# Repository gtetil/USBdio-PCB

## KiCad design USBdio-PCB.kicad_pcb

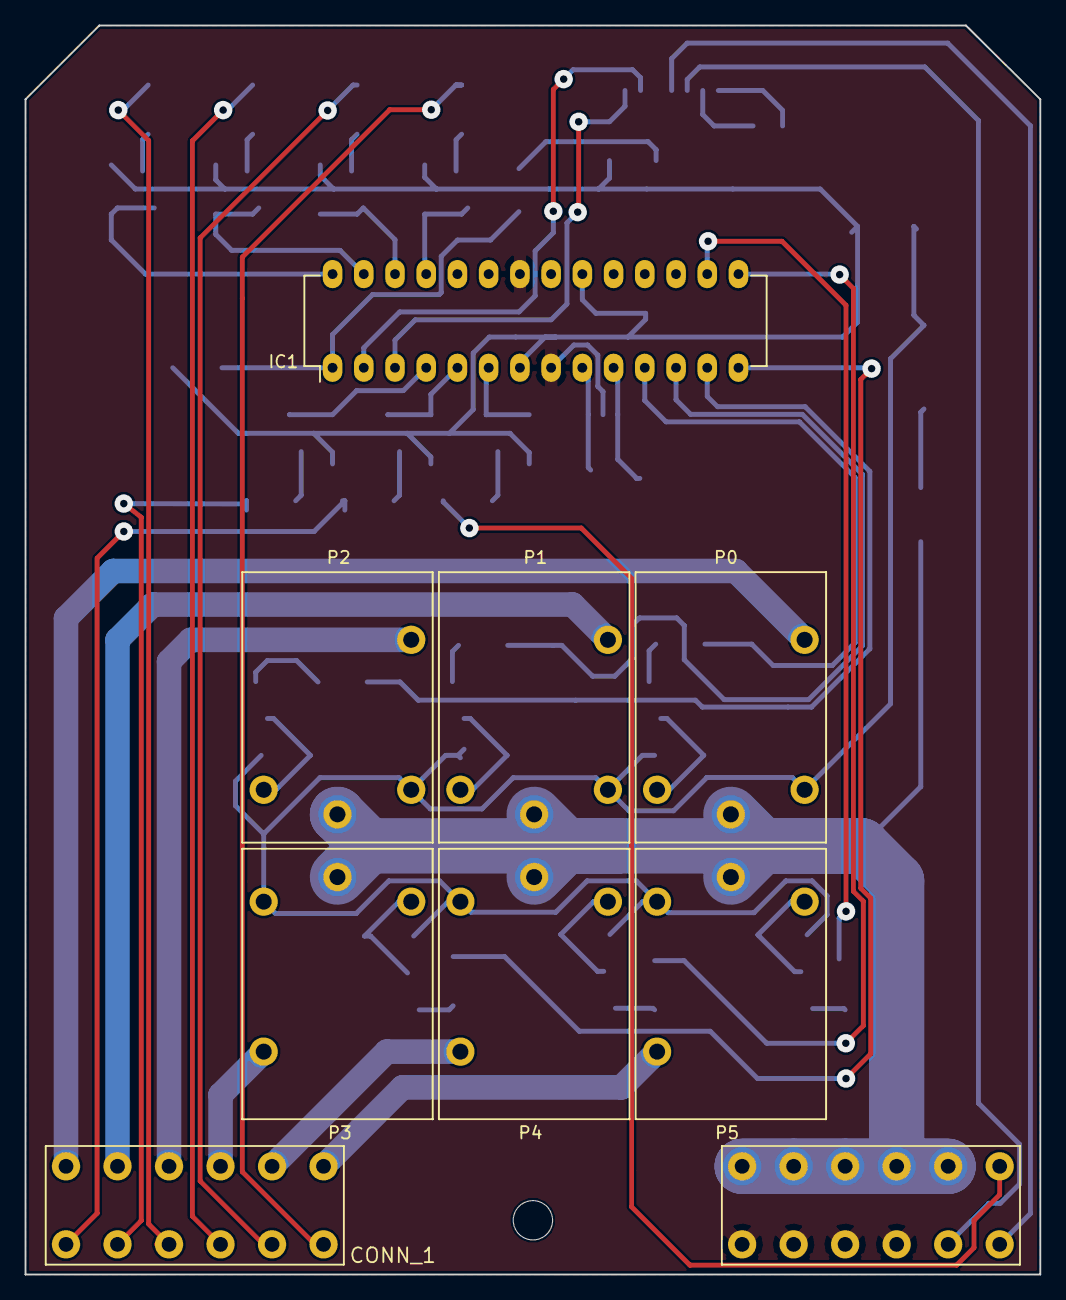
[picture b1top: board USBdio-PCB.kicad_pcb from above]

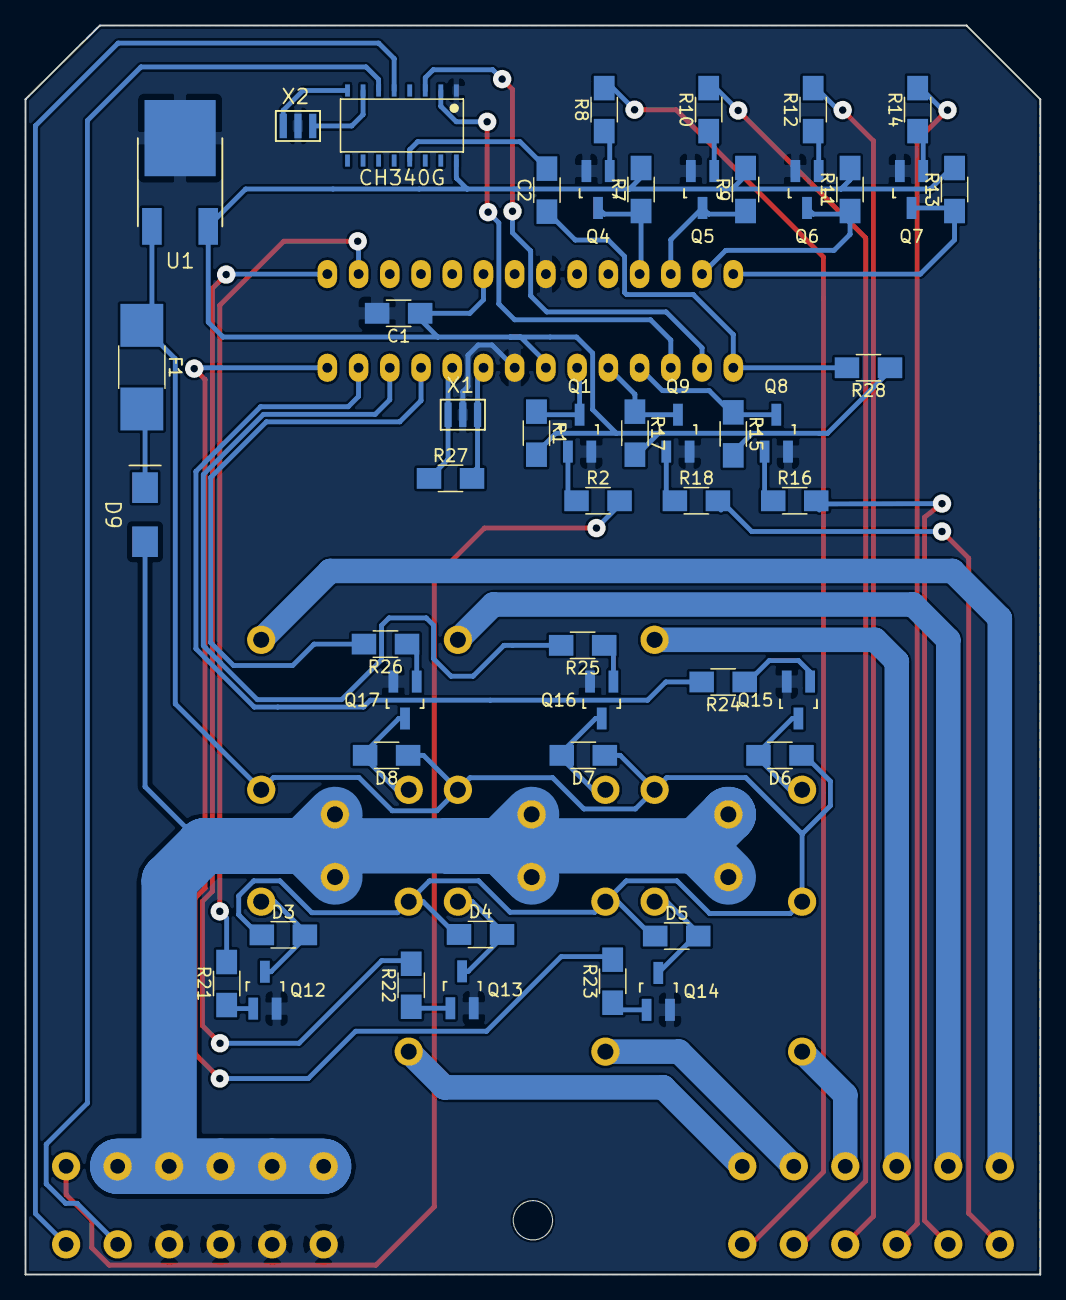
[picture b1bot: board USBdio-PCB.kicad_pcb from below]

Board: 2 copper layers, 82.5 x 101.6 mm, 57 parts (49 on the bottom side), 60 nets.

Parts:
C1, C2: 0.1uF; R_1206_HandSoldering_(narrow)
CONN_1: DEUTSCH_CONN_(DTM13-12PA-12PB-R008)
D3, D4, D5, D6, D7, D8: D; R_1206_HandSoldering_(narrow)
D9: D_Schottky; SCHOTTKY_(PMEG3030EP,115)
F1: Polyfuse; R_1812_HandSoldering
IC1: ATMEGA328-P; DIP-28_W7.62mm_LongPads
IC2: CH340G
P0, P1, P2, P3, P4, P5: RELAY_(JSM1A-12V-4)
Q1, Q4, Q5, Q6, Q7, Q8, Q9: Q_NPN_BEC; SOT-23_Handsoldering
Q12, Q13, Q14, Q15, Q16, Q17: Q_NPN; SOT-23_Handsoldering
R1, R2, R7, R8, R9, R10, R11, R12, R13, R14, R15, R16, R17, R18, R28: 10k; R_1206_HandSoldering_(narrow)
R21, R22, R23, R24, R25, R26: 680; R_1206_HandSoldering_(narrow)
R27: 1M; R_1206_HandSoldering_(narrow)
U1: NCV7805BDTRKG; REGULATOR_(NCV7805BDTRKG)
X1, X2: Crystal_GND2; RESONATOR_(CSTCE16M0V53C-R0)

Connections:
+5V: C1.1, IC1.7, IC1.20, IC2.16, R1.2, R7.2, R9.2, R11.2, R13.2, R15.2, R17.2, R28.1, U1.3
D+: CONN_1.B7, IC2.5
D-: CONN_1.B8, IC2.6
GND: C1.2, CONN_1.B9, CONN_1.B10, CONN_1.B11, CONN_1.B12, IC1.8, IC1.22, IC2.1, Q1.2, Q4.2, Q5.2, Q6.2, Q7.2, Q8.2, Q9.2, Q12.2, Q13.2, Q14.2, Q15.2, Q16.2, Q17.2, U1.2, X1.2, X2.2
unnamed: C2.1, IC1.1, R28.2
unnamed: C2.2, IC2.13
unnamed: CONN_1.A1, R8.2
unnamed: CONN_1.A2, R10.2
unnamed: CONN_1.A3, R12.2
unnamed: CONN_1.A4, R14.2
unnamed: CONN_1.A5, R16.2
unnamed: CONN_1.A6, R18.2
unnamed: CONN_1.B1, CONN_1.B2, CONN_1.B3, CONN_1.B4, CONN_1.B5, D9.2, P0.1, P1.1, P2.1, P3.1, P4.1, P5.1
unnamed: CONN_1.B6, R2.2
unnamed: D3.1, D4.1, D5.1, D6.1, D7.1, D8.1, F1.1, P0.2, P1.2, P2.2, P3.2, P4.2, P5.2, U1.1
unnamed: D3.2, P5.5, Q12.3
unnamed: D4.2, P4.5, Q13.3
unnamed: D5.2, P3.5, Q14.3
unnamed: D6.2, P2.5, Q15.3
unnamed: D7.2, P1.5, Q16.3
unnamed: D8.2, P0.5, Q17.3
unnamed: D9.1, F1.2
unnamed: IC1.4, Q8.3, R15.1
unnamed: IC1.5, Q9.3, R17.1
unnamed: IC1.6, Q1.3, R1.1
unnamed: IC1.9, R27.2, X1.1
unnamed: IC1.10, R27.1, X1.3
unnamed: IC1.11, R26.2
unnamed: IC1.12, R25.2
unnamed: IC1.13, R24.2
unnamed: IC1.14, R23.2
unnamed: IC1.15, R22.2
unnamed: IC1.16, R21.2
unnamed: IC1.25, Q4.3, R7.1
unnamed: IC1.26, Q5.3, R9.1
unnamed: IC1.27, Q6.3, R11.1
unnamed: IC1.28, Q7.3, R13.1
unnamed: IC2.7, X2.1
unnamed: IC2.8, X2.3
unnamed: Q1.1, R2.1
unnamed: Q4.1, R8.1
unnamed: Q5.1, R10.1
unnamed: Q6.1, R12.1
unnamed: Q7.1, R14.1
unnamed: Q8.1, R16.1
unnamed: Q9.1, R18.1
unnamed: Q12.1, R21.1
unnamed: Q13.1, R22.1
unnamed: Q14.1, R23.1
unnamed: Q15.1, R24.1
unnamed: Q16.1, R25.1
unnamed: Q17.1, R26.1
RLY0: CONN_1.A7, P0.3
RLY1: CONN_1.A8, P1.3
RLY2: CONN_1.A9, P2.3
RLY3: CONN_1.A10, P3.3
RLY4: CONN_1.A11, P4.3
RLY5: CONN_1.A12, P5.3
RXD: IC1.2, IC2.3
TXD: IC1.3, IC2.2

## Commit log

2016-08-10 added first connector
2016-08-10 added second connector
2016-08-10 modified text file
2016-08-29 finished schematic and created footprint for relay
2016-08-31 added remainder of footprints and 3D
2016-09-01 started laying out footprints
2016-09-03 finished first rev of PCB
2016-09-03 created gerbers
2016-09-04 created CircuitCAM and LMD files
2016-09-15 bigger pads for transistors and vias
2016-09-15 changed default traces from 0.2 mm to 0.4 mm
2016-09-20 removed ground planes
2016-10-24 initial commit of deutsch enclosure layout
2016-10-26 all footprints added. ready for traces.
2016-10-27 almost finish with traces.
2016-10-27 finished traces
2016-11-04 Reduced to 6 in 6 out, and added COM lines to connector.
2017-08-18 -added CH340G and a self-resetting fuse -corrected errors from v1.1
2017-08-21 created .cam file
2017-09-03 -Switched Tx and Rx. -Changed reset pull-up from 10kohm to 1kohm.
